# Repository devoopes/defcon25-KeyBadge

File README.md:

# KeyBadge
Defcon25 Key Badge

Badge printed with PLA to represent the Defcon 25 logo and theme. PCB on the back with ATTiny85 and two neopixels to illuminate the inside of the head.

- *KiCAD* files in KiCAD folder.
- *STL, OBJ, and SVG* in TinkerCAD folder.
- *Arduino* in Arduino folder.

### TinkerCAD design

### Painting Production

### PCB Assembly and Production

### Final Product

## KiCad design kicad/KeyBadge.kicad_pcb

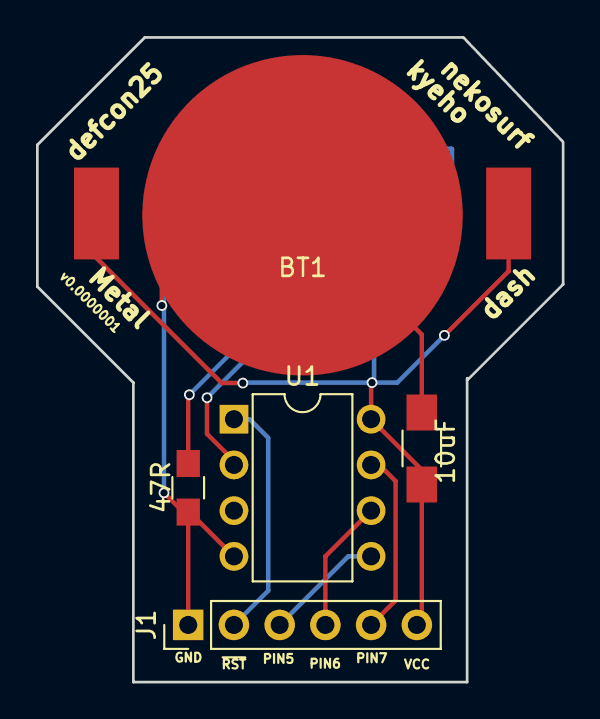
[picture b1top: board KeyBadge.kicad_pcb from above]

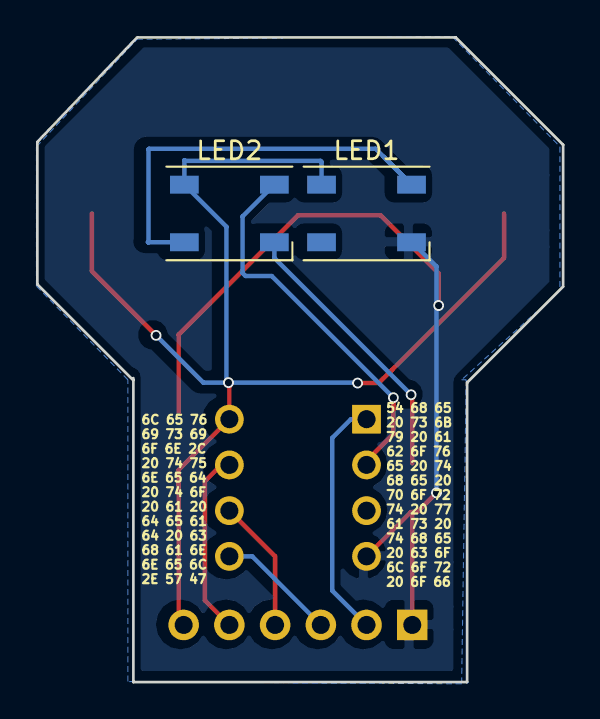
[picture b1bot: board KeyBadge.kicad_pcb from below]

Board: 2 copper layers, 29.2 x 35.8 mm, 7 parts (2 on the bottom side), 9 nets.

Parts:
10uF: CP1; R_1206_HandSoldering
47R: 47R; R_0805_HandSoldering
BT1: Battery_Cell; CR2025
J1: CONN_01X06; Pin_Header_Straight_1x06_Pitch2.54mm
LED1, LED2: WS2812B; LED_WS2812B-PLCC4
U1: ATTINY85-20PU; DIP-8_W7.62mm

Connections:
GND: 10uF.2, 47R.1, BT1.2, J1.1, LED1.3, U1.4
unnamed: J1.2, U1.1
unnamed: J1.3, U1.5
unnamed: J1.4, U1.6
unnamed: J1.5, U1.7
unnamed: LED1.4, LED2.2
unnamed: 47R.2, LED2.3
unnamed: LED2.4, U1.2
VCC: 10uF.1, BT1.1, J1.6, LED1.1, LED2.1, U1.8

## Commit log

2017-07-07 All the stuff
2017-07-07 fixing image
2017-07-07 Your Mac is leaking.
2017-07-25 Arduino code
2017-07-25 GRB not RGB
2017-07-25 a little helper for reading the text on the front of the board.
2018-03-27 Fixing logo
2018-03-28 fixing some stuff and adding the footprint for ws2812b
2018-05-03 Cleanup and photos
2018-05-03 Helps to add file extensions in path
2018-05-03 Adding tags for photos.
2018-05-25 Not sure why this wasn't int he right folder.
